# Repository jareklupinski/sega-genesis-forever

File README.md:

# sega-genesis-forever
A Standalone Sega Genesis music player using native hardware

Using an ATSAMD21 microcontroller, this gadget reads Sega Genesis VGM files from a microSD card and plays them back using the same sound chips that were used in the original Sega Genesis. Even the audio path is cloned from original schematics!

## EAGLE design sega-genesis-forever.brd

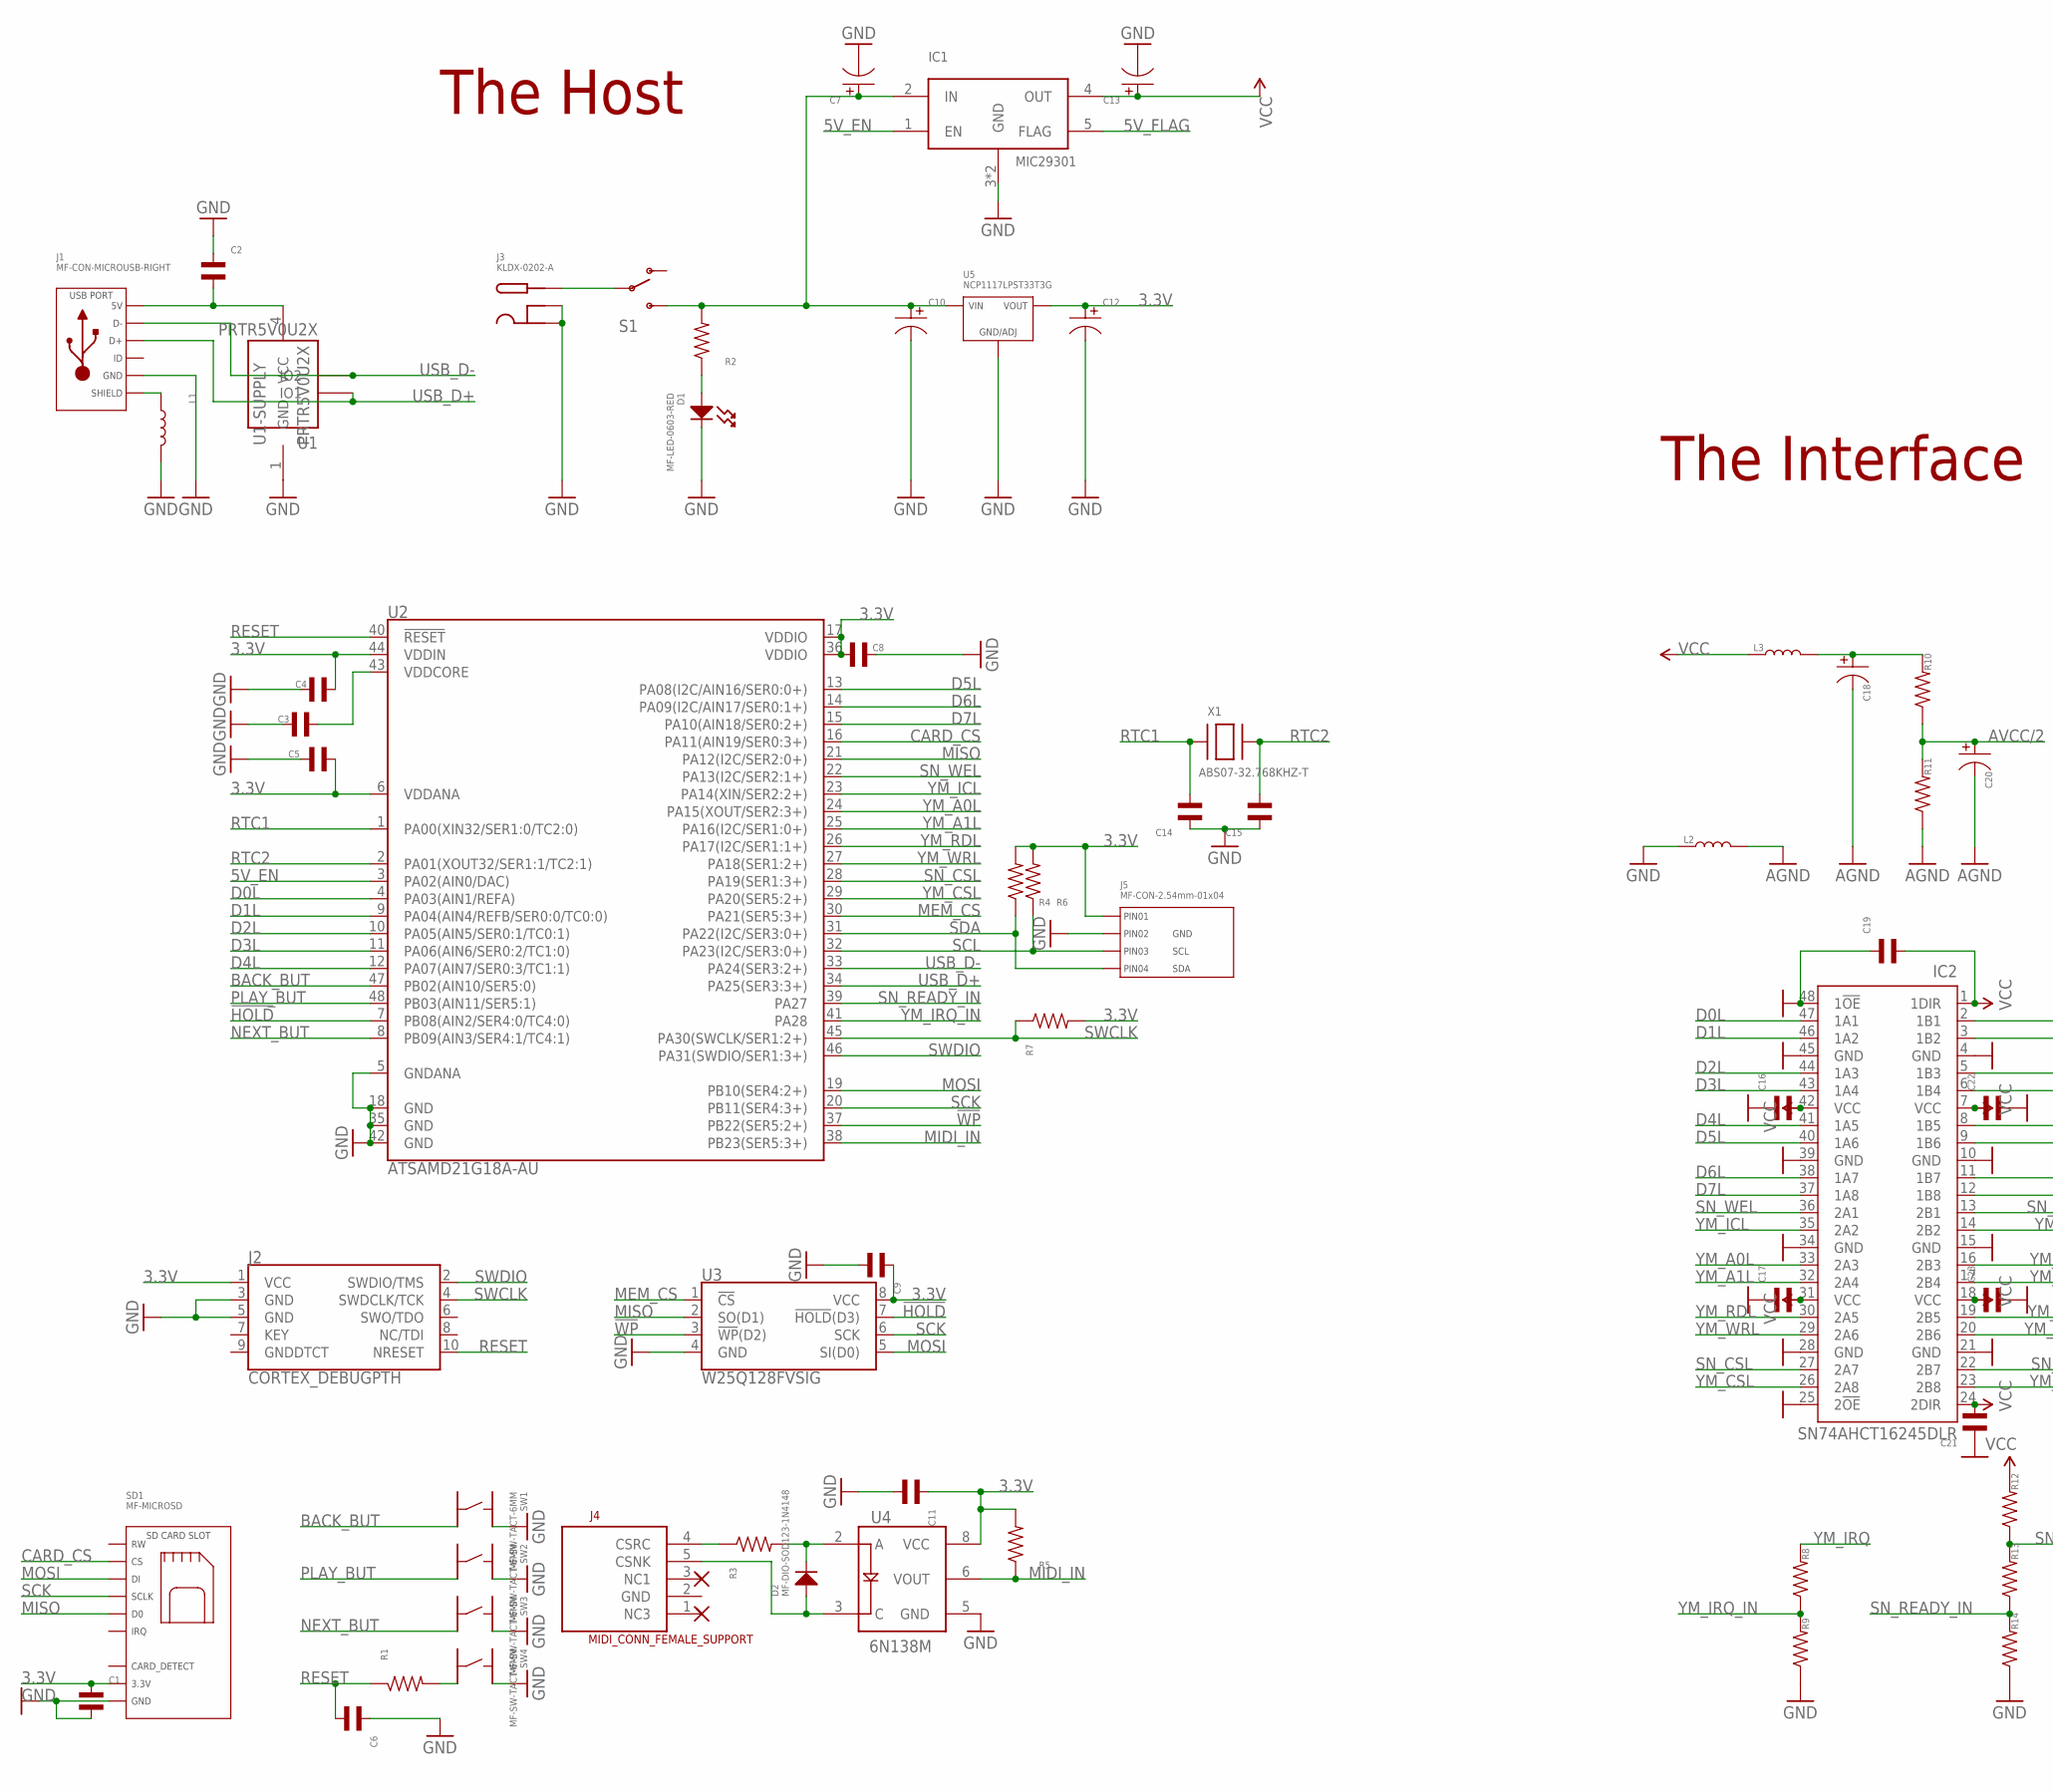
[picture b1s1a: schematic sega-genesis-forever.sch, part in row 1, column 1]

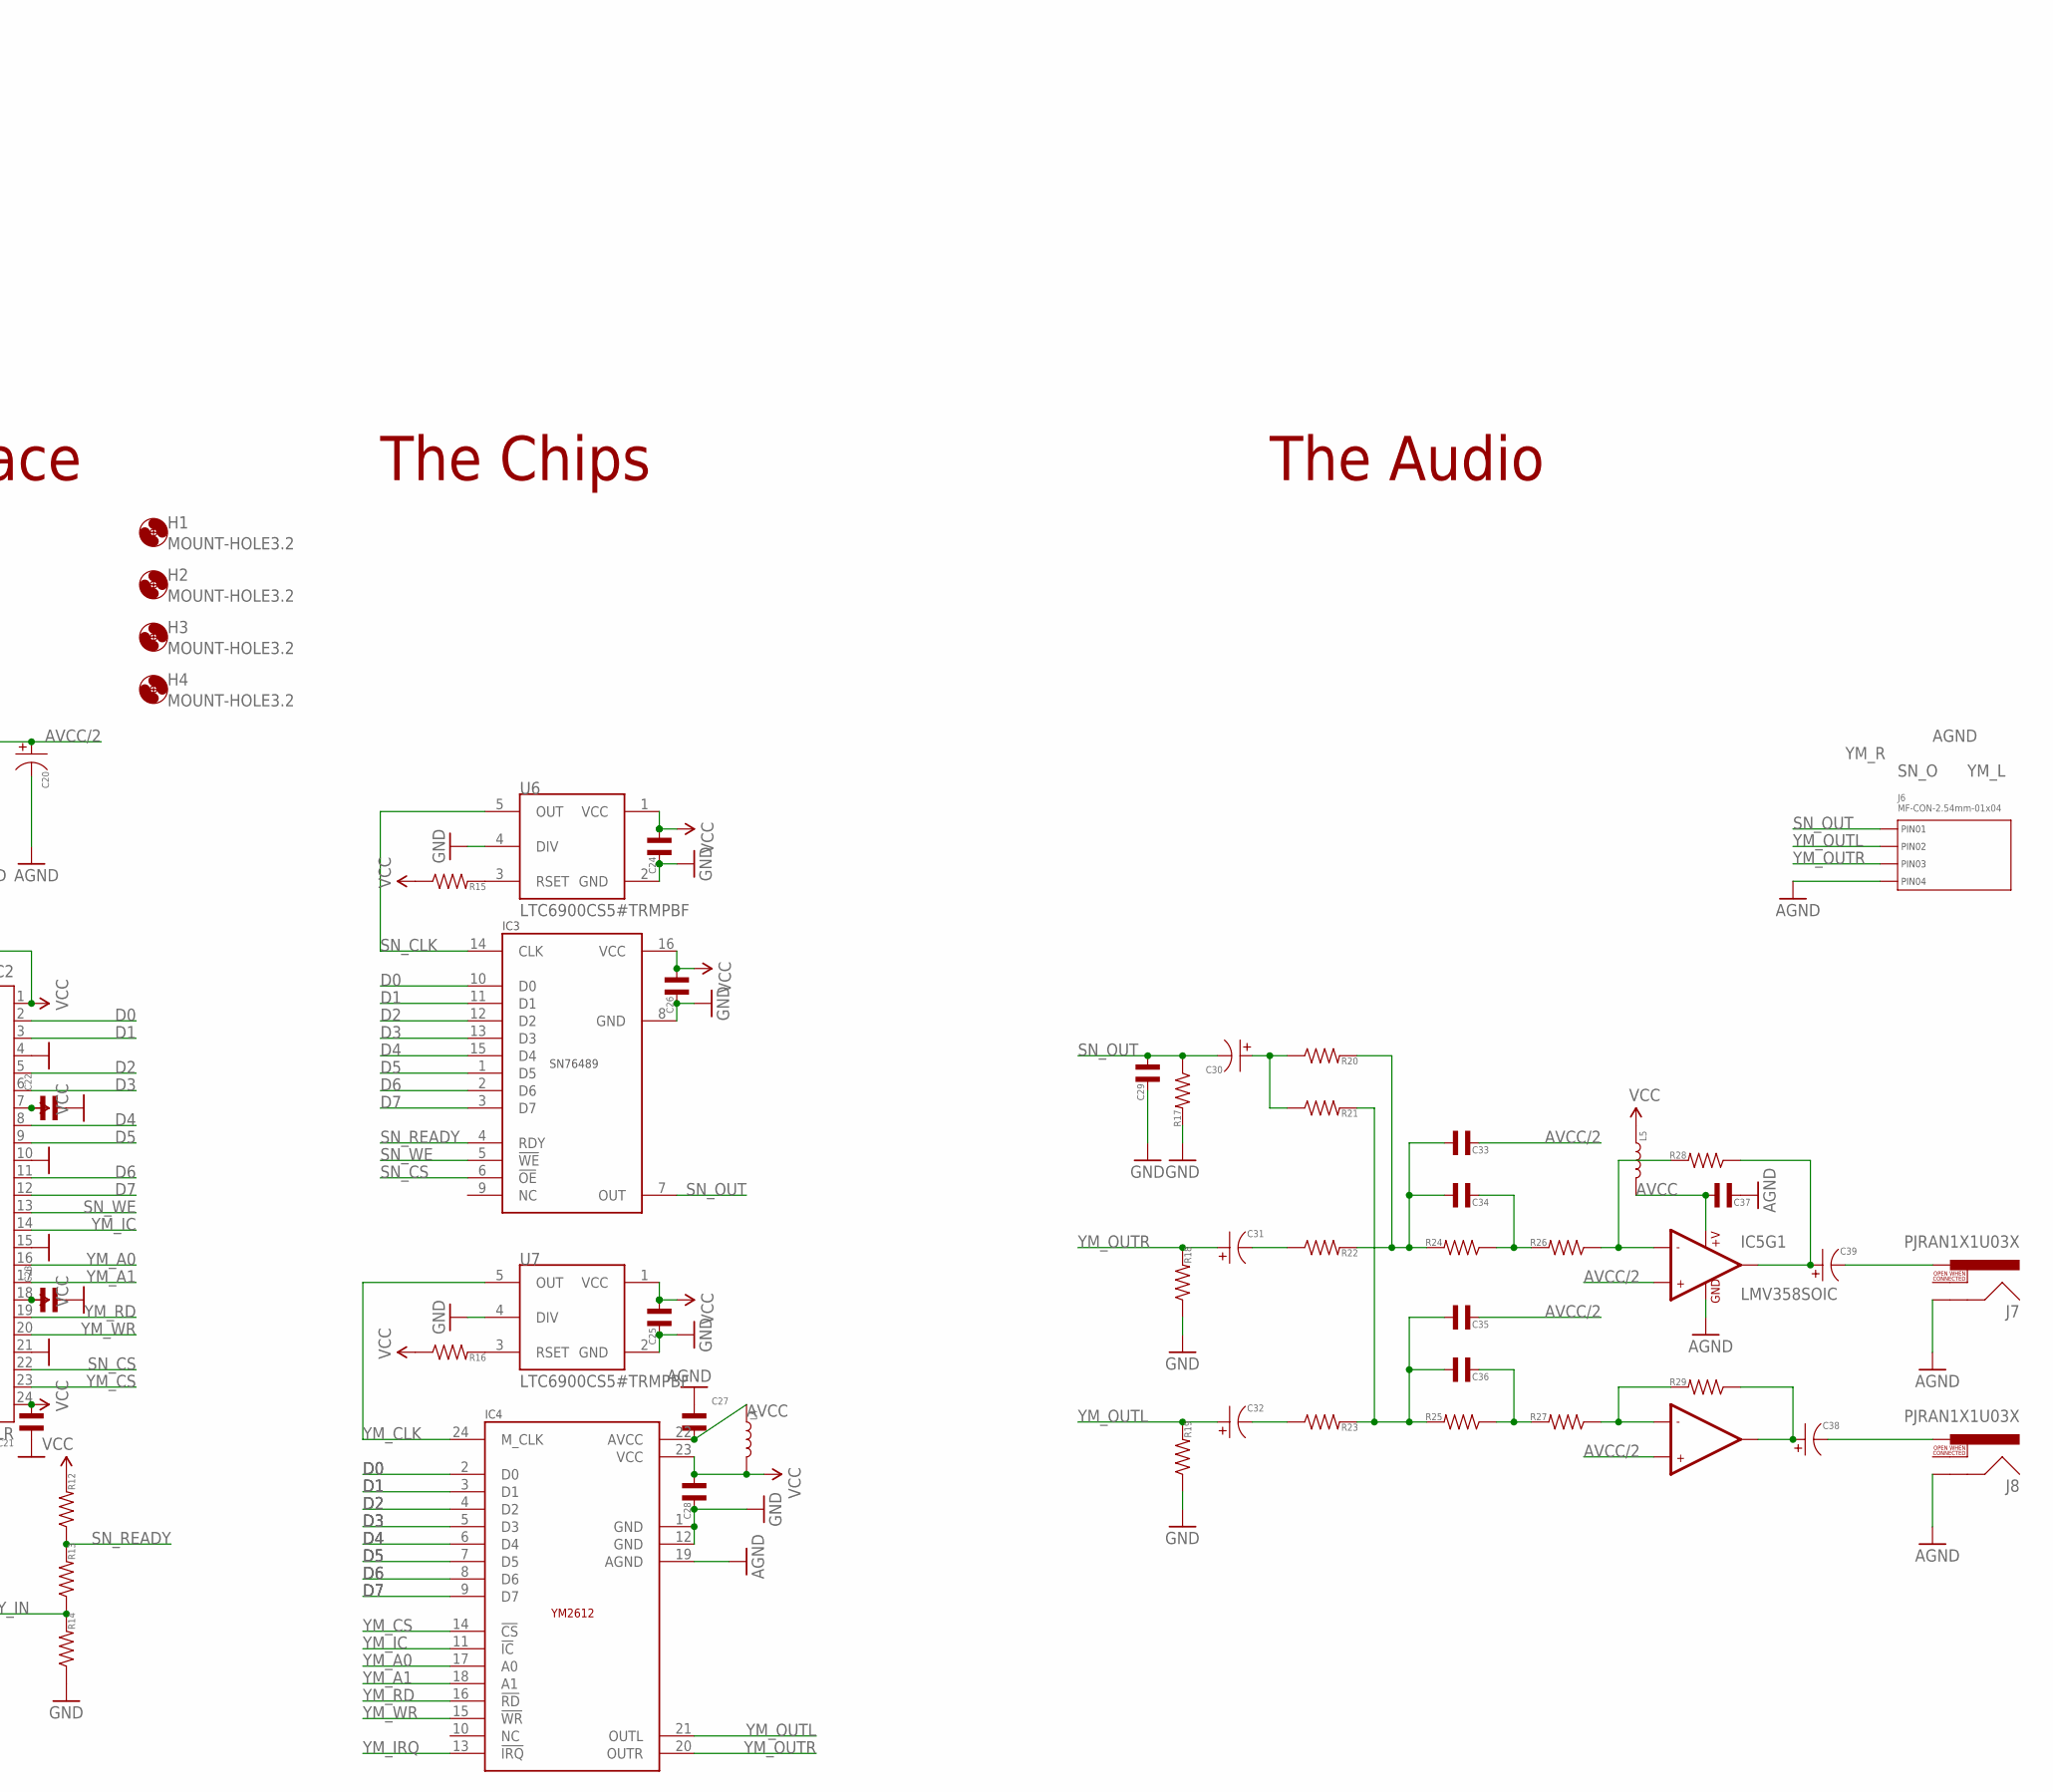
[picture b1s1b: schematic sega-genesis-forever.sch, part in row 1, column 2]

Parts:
C1, C2, C3, C4, C5, C6, C8, C9, C11, C14, C15, C16, C17, C19, C21, C22, C23, C24, C25, C26, C27, C28, C29, C33, C34, C35, C36, C37: CAPACITOR_NP_0603; C0603
C7, C10, C12, C13, C18, C30, C31, C32, C38, C39: CAPACITOR_P_4MM; CP4MM
C20: CAPACITOR_P_6.3MM; CP6.3MM
D1: MF-LED-0603-RED; LED0603
D2: MF-DIO-SOD123-1N4148; SOD-123
H1, H2, H3, H4: MOUNT-HOLE3.2; 3,2
IC1: MIC29301; TO263-5
IC2: SN74AHCT16245DLR; DL_R-PDSO-G48
IC3: ED16DT; DIL16-EZ
IC4: ED24DT; DIL24-EZ
IC5: LMV358SOIC; SO08
J1: MF-CON-MICROUSB-RIGHT; MICROUSB-RIGHT
J2: CORTEX_DEBUGPTH; 2X5-PTH-1.27MM
J3: KLDX-0202-A; DC_PWR_JACK
J4: MIDI_CONN_FEMALE_SUPPORT; DIN_5_FEMALE_SUPPORT
J5, J6: MF-CON-2.54mm-01x04; PTH_2.54MM_01X04
J7, J8: PJRAN1X1U03X; RCA
L1: INDUCTOR_1210; L1210
L2, L3, L4, L5: INDUCTOR_0603; L0603
R1, R2, R3, R4, R5, R6, R7, R8, R9, R10, R11, R12, R13, R14, R15, R16, R17, R18, R19, R20, R21, R22, R23, R24, R25, R26, R27, R28, R29: RESISTOR_0603; R0603
S1: SWITCH-SPDTPTH; SWITCH-SPDT
SD1: MF-MICROSD
SW1, SW2, SW3, SW4: MF-SW-TACT-6MM; TACT6MM
U1: PRTR5V0U2X; SOT-143B
U2: ATSAMD21G18A-AU; TQFP-48
U3: W25Q128FVSIG; SOIC-8
U4: 6N138M; 8-SMD
U5: NCP1117LPST33T3G; SOT-223-3
U6, U7: LTC6900CS5#TRMPBF; TSOT23-5L
X1: ABS07-32.768KHZ-T; XTAL3215

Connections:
3.3V: C1.P$1, C4.P$2, C5.P$2, C8.P$2, C9.P$1, C11.P$1, C12.P$1, J2.1 (VCC), J5.P$1 (PIN1), R4.P$2, R5.P$2, R6.P$2, R7.P$2, SD1.PIN4 (3.3V), U2.6 (VDDANA), U2.17 (VDDIO), U2.36 (VDDIO), U2.44 (VDDIN), U3.8 (VCC), U4.8 (VCC), U5.P$1 (VOUT), U5.P$3 (VOUT)
5V_EN: IC1.1 (EN), U2.3 (PA02(AIN0/DAC))
5V_FLAG: IC1.5 (FLAG)
!HOLD: U2.7 (PB08(AIN2/SER4:0/TC4:0)), U3.7 (!HOLD!(D3))
!WP: U2.37 (PB22(SER5:2+)), U3.3 (!WP!(D2))
AGND: C18.P$2, C20.P$2, C27.P$1, C37.P$2, IC4.19 (AGND), IC5.4 (GND), J6.P$4 (PIN4), J7.SHELL, J8.SHELL, L2.P$2, R11.P$1
AVCC: C27.P$2, C37.P$1, IC4.22 (AVCC), IC5.8 (+V), L4.P$1, L5.P$2
AVCC/2: C20.P$1, C33.P$2, C35.P$2, IC5.3 (+IN1), IC5.5 (+IN2), R10.P$1, R11.P$2
BACK_BUT: SW1.P$4, U2.47 (PB02(AIN10/SER5:0))
CARD_CS: SD1.PIN2 (CS), U2.16 (PA11(AIN19/SER0:3+))
D0: IC2.2 (1B1), IC3.10 (D0), IC4.2 (D0)
D0L: IC2.47 (1A1), U2.4 (PA03(AIN1/REFA))
D1: IC2.3 (1B2), IC3.11 (D1), IC4.3 (D1)
D1L: IC2.46 (1A2), U2.9 (PA04(AIN4/REFB/SER0:0/TC0:0))
D2: IC2.5 (1B3), IC3.12 (D2), IC4.4 (D2)
D2L: IC2.44 (1A3), U2.10 (PA05(AIN5/SER0:1/TC0:1))
D3: IC2.6 (1B4), IC3.13 (D3), IC4.5 (D3)
D3L: IC2.43 (1A4), U2.11 (PA06(AIN6/SER0:2/TC1:0))
D4: IC2.8 (1B5), IC3.15 (D4), IC4.6 (D4)
D4L: IC2.41 (1A5), U2.12 (PA07(AIN7/SER0:3/TC1:1))
D5: IC2.9 (1B6), IC3.1 (D5), IC4.7 (D5)
D5L: IC2.40 (1A6), U2.13 (PA08(I2C/AIN16/SER0:0+))
D6: IC2.11 (1B7), IC3.2 (D6), IC4.8 (D6)
D6L: IC2.38 (1A7), U2.14 (PA09(I2C/AIN17/SER0:1+))
D7: IC2.12 (1B8), IC3.3 (D7), IC4.9 (D7)
D7L: IC2.37 (1A8), U2.15 (PA10(AIN18/SER0:2+))
GND: C1.P$2, C2.P$1, C3.P$2, C4.P$1, C5.P$1, C6.P$1, C7.P$2, C8.P$1, C9.P$2, C10.P$2, C11.P$2, C12.P$2, C13.P$2, C14.P$1, C15.P$1, C16.P$1, C17.P$1, C19.P$1, C21.P$1, C22.P$2, C23.P$2, C24.P$2, C25.P$2, C26.P$2, C28.P$2, C29.P$2, D1.CATHODE, IC1.3 (GND), IC1.6 (GND), IC2.4 (GND), IC2.10 (GND), IC2.15 (GND), IC2.21 (GND), IC2.25 (2!OE), IC2.28 (GND), IC2.34 (GND), IC2.39 (GND), IC2.45 (GND), IC2.48 (1!OE), IC3.8 (GND), IC4.1 (GND), IC4.12 (GND), J1.5 (GND), J2.3 (GND), J2.5 (GND), J3.SLEEVE1 (SLEEVE), J3.SLEEVE2 (SLEEVE_SHUNT), J5.P$2 (PIN2), L1.P$2, L2.P$1, R9.P$1, R14.P$1, R17.P$2, R18.P$1, R19.P$1, SD1.G0 (GND), SD1.G1 (GND), SD1.PIN6 (GND), SW1.P$2, SW2.P$2, SW3.P$2, SW4.P$2, U1.1 (GND), U2.5 (GNDANA), U2.18 (GND), U2.35 (GND), U2.42 (GND), U3.4 (GND), U4.5 (GND), U5.P$2 (GND/ADJ), U6.2 (GND), U6.4 (DIV), U7.2 (GND), U7.4 (DIV)
LADC: IC5.6 (-IN2), R27.P$1, R29.P$2
MEM_CS: U2.30 (PA21(SER5:3+)), U3.1 (!CS!)
MIDI_IN: R5.P$1, U2.38 (PB23(SER5:3+)), U4.6 (VOUT)
MISO: SD1.PIN7 (D0), U2.21 (PA12(I2C/SER2:0+)), U3.2 (SO(D1))
MOSI: SD1.PIN3 (DI), U2.19 (PB10(SER4:2+)), U3.5 (SI(D0))
unnamed: C30.P$1, R20.P$1, R21.P$1
unnamed: C31.P$2, R22.P$1
unnamed: C32.P$2, R23.P$1
unnamed: C33.P$1, C34.P$1, R20.P$2, R22.P$2, R24.P$2
unnamed: C35.P$1, C36.P$1, R21.P$2, R23.P$2, R25.P$2
unnamed: C39.P$1, IC5.1 (OUT1), R28.P$1
unnamed: J4.4 (CSRC), R3.P$1
unnamed: C3.P$1, U2.43 (VDDCORE)
unnamed: R1.P$2, SW4.P$4
unnamed: J1.S1 (SLD), J1.S2 (SLD), J1.S3 (SLD), J1.S4 (SLD), J1.S5 (SLD), J1.S6 (SLD), L1.P$1
unnamed: C38.P$1, IC5.7 (OUT2), R29.P$1
unnamed: C34.P$2, R24.P$1, R26.P$2
unnamed: D2.CATHODE, R3.P$2, U4.2 (A)
unnamed: D2.ANODE, J4.5 (CSNK), U4.3 (C)
unnamed: C39.P$2, J7.PIN
unnamed: C36.P$2, R25.P$1, R27.P$2
unnamed: D1.ANODE, R2.P$1
unnamed: C18.P$1, L3.P$2, R10.P$2
unnamed: C38.P$2, J8.PIN
unnamed: C7.P$1, C10.P$1, IC1.2 (IN), R2.P$2, S1.3 (S), U5.P$4 (VIN)
unnamed: J3.PIN, S1.2
unnamed: R16.P$2, U7.3 (RSET)
unnamed: R15.P$2, U6.3 (RSET)
unnamed: C2.P$2, J1.1 (5V), U1.4 (VCC)
NEXT_BUT: SW3.P$4, U2.8 (PB09(AIN3/SER4:1/TC4:1))
PLAY_BUT: SW2.P$4, U2.48 (PB03(AIN11/SER5:1))
RADC: IC5.2 (-IN1), R26.P$1, R28.P$2
RESET: C6.P$2, J2.10 (NRESET), R1.P$1, U2.40 (!RESET!)
RTC1: C14.P$2, U2.1 (PA00(XIN32/SER1:0/TC2:0)), X1.P$1
RTC2: C15.P$2, U2.2 (PA01(XOUT32/SER1:1/TC2:1)), X1.P$2
SCK: SD1.PIN5 (SCLK), U2.20 (PB11(SER4:3+)), U3.6 (SCK)
SCL: J5.P$3 (PIN3), R6.P$1, U2.32 (PA23(I2C/SER3:0+))
SDA: J5.P$4 (PIN4), R4.P$1, U2.31 (PA22(I2C/SER3:0+))
SN_CLK: IC3.14 (CLK), U6.5 (OUT)
SN_CS: IC2.22 (2B7), IC3.6 (!OE)
SN_CSL: IC2.27 (2A7), U2.28 (PA19(SER1:3+))
SN_OUT: C29.P$1, C30.P$2, IC3.7 (OUT), J6.P$1 (PIN1), R17.P$1
SN_READY: IC3.4 (RDY), R12.P$1, R13.P$2
SN_READY_IN: R13.P$1, R14.P$2, U2.39 (PA27)
SN_WE: IC2.13 (2B1), IC3.5 (!WE)
SN_WEL: IC2.36 (2A1), U2.22 (PA13(I2C/SER2:1+))
SWCLK: J2.4 (SWDCLK/TCK), R7.P$1, U2.45 (PA30(SWCLK/SER1:2+))
SWDIO: J2.2 (SWDIO/TMS), U2.46 (PA31(SWDIO/SER1:3+))
USB_D+: J1.3 (D+), U1.2 (IO1), U2.34 (PA25(SER3:3+))
USB_D-: J1.2 (D-), U1.3 (IO2), U2.33 (PA24(SER3:2+))
VCC: C13.P$1, C16.P$2, C17.P$2, C19.P$2, C21.P$2, C22.P$1, C23.P$1, C24.P$1, C25.P$1, C26.P$1, C28.P$1, IC1.4 (OUT), IC2.1 (1DIR), IC2.7 (VCC), IC2.18 (VCC), IC2.24 (2DIR), IC2.31 (VCC), IC2.42 (VCC), IC3.16 (VCC), IC4.23 (VCC), L3.P$1, L4.P$2, L5.P$1, R12.P$2, R15.P$1, R16.P$1, U6.1 (VCC), U7.1 (VCC)
YM_A0: IC2.16 (2B3), IC4.17 (A0)
YM_A0L: IC2.33 (2A3), U2.24 (PA15(XOUT/SER2:3+))
YM_A1: IC2.17 (2B4), IC4.18 (A1)
YM_A1L: IC2.32 (2A4), U2.25 (PA16(I2C/SER1:0+))
YM_CLK: IC4.24 (M_CLK), U7.5 (OUT)
YM_CS: IC2.23 (2B8), IC4.14 (!CS)
YM_CSL: IC2.26 (2A8), U2.29 (PA20(SER5:2+))
YM_IC: IC2.14 (2B2), IC4.11 (!IC)
YM_ICL: IC2.35 (2A2), U2.23 (PA14(XIN/SER2:2+))
YM_IRQ: IC4.13 (!IRQ), R8.P$2
YM_IRQ_IN: R8.P$1, R9.P$2, U2.41 (PA28)
YM_OUTL: C32.P$1, IC4.21 (OUTL), J6.P$2 (PIN2), R19.P$2
YM_OUTR: C31.P$1, IC4.20 (OUTR), J6.P$3 (PIN3), R18.P$2
YM_RD: IC2.19 (2B5), IC4.16 (!RD)
YM_RDL: IC2.30 (2A5), U2.26 (PA17(I2C/SER1:1+))
YM_WR: IC2.20 (2B6), IC4.15 (!WR)
YM_WRL: IC2.29 (2A6), U2.27 (PA18(SER1:2+))

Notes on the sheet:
The Host
The Interface
The Chips
The Audio

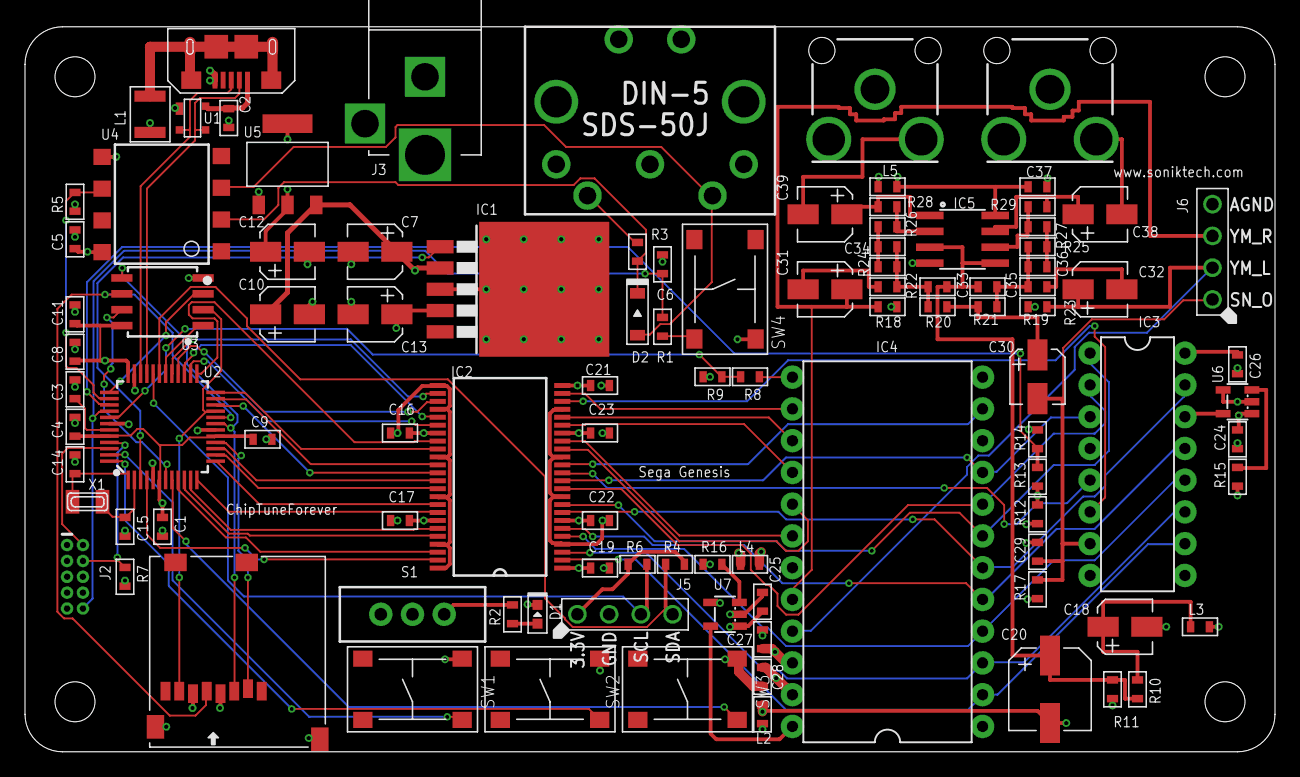
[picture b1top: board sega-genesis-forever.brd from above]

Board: 4 copper layers, 100.0 x 58.0 mm, 106 parts (0 on the bottom side), 94 nets.

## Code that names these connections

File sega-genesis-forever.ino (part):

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#define RELEASE      0xAB
#define BLOCK64ERASE 0xD8
//PORTA
#define CARD_CS ( 1 << 11 ) // 0
#define MISO    ( 1 << 12 ) // 0
#define SN_WE   ( 1 << 13 ) // 1
#define YM_IC   ( 1 << 14 ) // 1
#define YM_A0   ( 1 << 15 ) // 0
#define YM_A1   ( 1 << 16 ) // 0
#define YM_RD   ( 1 << 17 ) // 1
#define YM_WR   ( 1 << 18 ) // 1
#define SN_CS   ( 1 << 19 ) // 1
#define YM_CS   ( 1 << 20 ) // 1
#define MEM_CS  ( 1 << 21 ) // 1
#define SDA     ( 1 << 22 ) // 1
#define SCL     ( 1 << 23 ) // 1
#define SN_RDY  ( 1 << 27 ) // 1
#define YM_IRQ  ( 1 << 28 ) // 1
//PORTB
#define BACKBUTTON        ( 1 << 2 ) // 1
#define BACKARDUINO       19
#define PLAYBUTTON        ( 1 << 3 ) // 1
#define PLAYARDUINO       25
#define HOLD              ( 1 << 8 ) // 0
#define NEXTBUTTON        ( 1 << 9 ) // 1
#define NEXTARDUINO       16
#define MOSI              ( 1 << 10 ) // 0
#define SCK               ( 1 << 11 ) // 0
#define MEM_WP            ( 1 << 22 ) // 1
#define MIDI_IN           ( 1 << 23 ) // 1
//DEBUG
#ifdef DEBUG
#define DEBUG_PRINT(...)   Serial.print(__VA_ARGS__)
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
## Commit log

2018-07-05 design tested: working

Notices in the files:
parts and their libraries:
SparkFun-Connectors: Licensing: Creative Commons ShareAlike 4.0 International - https://creativecommons.org/licenses/by-sa/4.0
SparkFun-DiscreteSemi: Licensing: CC v3.0 Share-Alike You are welcome to use this library for commercial purposes.
